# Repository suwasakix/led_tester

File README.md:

# LED Tester

LED テスター

&nbsp;

## 目次 - Contents

 - [このプリント基板について](#このプリント基板について---about-this-pcb)
 - [ガーバーデータのダウンロード](#ガーバーデータのダウンロード---download-gerber-data)
 - [回路図](#回路図---pcb-schematic)
 - [レイアウト](#レイアウト---pcb-layout)
 - [部品リスト](#部品リスト---parts-list)
 - [便利なアイテム](#便利なアイテム---useful-items)
 - [使用例](#使用例---example-of-use)
 - [開発環境](#開発環境---development-environment)
 - [ライセンスについて](#ライセンスについて---license)

&nbsp;

## このプリント基板について - About this PCB

このプリント基板は、LED のテスター回路を実装したものです。  

この基板はボリュームで電流値をコントロール可能な定電流回路を実装しており、電流に応じた LED の照度や順方向電圧の確認に使用することができます。  

念のために書いておくと、[OptoSupply の LED テスター][AK_101860_LED_TESTER] が秋月電子通商で売っています。どちらを選ぶかはお好みで。  

&nbsp;

【 測定用基板シリーズ 】  

- [定電流ダイオード/定電圧ダイオード/FET 簡易測定器](https://github.com/suwasakix/simple_crd_zd_fet_tester)  
- [トランジスタ hFE 簡易測定器](https://github.com/suwasakix/simple_hfe_tester)  
- [FET バイアス測定器](https://github.com/suwasakix/fet_bias_tester)  
- LED テスター  

&nbsp;

## ガーバーデータのダウンロード - Download gerber data

こちらのページから「led_tester-gerber.zip」のファイルをダウンロードしてください。  

&emsp; https://www.github.com/suwasakix/led_tester/releases

このプロジェクトは、各自がプリント基板のガーバーデータをダウンロードして PCB 基板メーカーに基板製造を発注することを前提にしています。個人で発注可能な PCB 基板メーカーは国内外問わずありますが、近年では 10cm 四方以下の基板サイズであれば海外メーカーで格安に製造委託することが可能になりました。発注例として、深圳の Seeed studio が提供する PCB 製造サービス「[Fusion PCB](https://www.fusionpcb.jp)」に基板製造を発注する方法を[こちらのページ](docs/ORDER_PCB.md)で紹介しておきます。  

&nbsp;

## 回路図 - PCB schematic

定電流回路はオペアンプを使用したオーソドックスな回路です。オペアンプには差動入力（＋端子と－端子）が同じ電圧となろうとする性質があるので、LED に電流が流ているとき VR1 の両端にかかる電圧と R1 の両端にかかる電圧はほぼ同じ値になります（R2 に電流はほとんど流れません）。VR1 を調整することによって LED に流れる電流をコントロールすることができるという仕組みです。  

Vcc (9V) を 12.4kΩ と 10kΩ で分圧したとき 10kΩ には約4V の電圧がかかることになるので、VR1 を調整することによって LED に流れる電流を最大 40mA 程度にまで変えることが可能です。ですが、最大電流が大きいと 1mA 単位の調整が難しくなるので、R4 を 18kΩ～22kΩ にして最大 20mA くらいにした方が使いやすいかもしれません。分圧比は各自の好みに応じて変更して頂いて問題ありませんが、最大電流は 50mA を超えないようにしてください。  

R1 は電流値を測定するための抵抗なので高精度品か、あるいは抵抗値を実測してなるべく 100Ω に近いものを使用してください。ワット数は 1/2W 以上のものを使用してください。  

R2 は他の作例を参考にして入れたものですが、おそらく 0Ω でも問題なく動作すると思います。  

VR1 には秋月電子通商で取り扱いのある基板取付用ボリューム RK09D117000B を採用しました。ボリュームの軸が長いので鋸などで軸を切って使用する場合には、必ず軸側を保持して切り落とすようにしてください。ボリューム本体側を保持して軸を切ろうとすると、ボリュームにストレスがかかって故障の原因になります。  

電源には 12V または 15V の AC アダプターを使用してください。DC ジャックは 外径 5.5mm / 内径 2.1mm センタープラスのものが適合します。 

&nbsp;

## レイアウト - PCB layout

* 基板サイズ : W 70mm × H 70mm

&nbsp;

## 部品リスト - Parts list

* 通販による部品販売では、10個単位などでまとめ売りされている場合がしばしばあります。注文の際にはご注意ください。
* ★ は省略可。
* ☆ は使用しなければ省略可。

|部品種別			|記号					|部品名															|値				|個数		|入手ルート																											|
|:----:				|:----:					|:----:															|:----:			|:----:		|:----:																												|
|抵抗				|R1						|金属皮膜抵抗 1/2W												|100Ω			|1			|[高精度 金属皮膜抵抗 1/2W100Ω ±0.1%][AK_108509_R100]																|
|					|R2, R3					|金属皮膜抵抗 1/4W												|10kΩ			|2			|[超小型 金属皮膜抵抗 1W10kΩ 1袋100本入][AK_108839_R10k]															|
|					|R4						|金属皮膜抵抗 1/4W												|2.2kΩ～2.4kΩ	|1			|[超小型 金属皮膜抵抗 1W2.2kΩ 1袋100本入][AK_108832_R2.2k]															|
|ボリューム			|VR1					|基板取付用ボリューム 10kΩBカーブ<br>RK09D117000B				|10kΩ			|1			|[基板取付用ボリューム 10kΩB][AK_114827_VR10kB_RK09D117000B]<br>[ボリューム用ツマミ][AK_C_CKNOB]					|
|コンデンサ			|C1						|電解コンデンサ<br>(直径 6.3mm,<br>リードピッチ 2.5mm)			|100μF			|1			|[100μF35V105℃ ルビコンZLH][AK_102724_C35v100u]																	|
|					|C2						|積層セラミックコンデンサ<br>(リードピッチ 2.54mm)				|0.33μF		|1			|[積層セラミックコンデンサー 0.33μF50V X7R 2.54mmピッチ][AK_115937_C50v0.33u]										|
|					|C3						|積層セラミックコンデンサ<br>(リードピッチ 2.54mm)				|0.1μF			|1			|[積層セラミックコンデンサー 0.1μF50V X7R 2.54mm][AK_113582_C50v0.1u]												|
|FET				|Q1						|BS170															|-				|1			|[Nch MOSFET BS170-D27Z][AK_130394_BS170]																			|
|IC					|U1						|２回路単電源オペアンプ<br>LM358/LM2904							|-				|1			|[2回路入汎用オペアンプ NJM2904D][AK_109216_NJM2904D]																|
|					|U2						|TO-220型 9V ３端子レギュレータ									|-				|1			|[三端子レギュレーター 9V1.5A NJM7809FA][AK_100162_NJM7809FA]														|
|スイッチ			|SW1 ★					|トグルスイッチ<br>(3P 1回路2接点 ON-ON)						|-				|1			|[2MS1-T1-B4-M2-Q-E][AK_102399_SW_2MS1-T1-B4-M2-Q-E]<br>[2MS1-T1-B4-VS2-Q-E-S][AK_100300_SW_2MS1-T1-B4-VS2-Q-E-S]	|
|チェック端子		|TP1 ～ TP5 ☆			|チェック端子													|-				|5			|[チェック端子][AK_C_CCHECKTER]																						|
|ソケット			|J1						|基板型DCジャック<br>(内径2.1mm, 外径5.5mm, 定格15V以上)		|-				|1			|[2DC0005D100 1パック4個入][AK_101604_2DC0005D100]																	|
|					|J2 ☆					|8ピン 板バネICソケット											|-				|1			|[2227-08-03 1パック10個入][AK_100017_2227-08-03]																	|
|基板スペーサー		|						|黄銅六角スペーサー<br>M3×10mm									|-				|4			|[FB3-10][AK_107313_FB3-10]																							|
|					|						|M3 ネジ								 						|-				|4			|(ホームセンター等で入手可能)																						|

[AK_108509_R100]:								https://akizukidenshi.com/catalog/g/g108509/
[AK_108832_R2.2k]:								https://akizukidenshi.com/catalog/g/g108832/
[AK_108839_R10k]:								https://akizukidenshi.com/catalog/g/g108839/
[AK_114827_VR10kB_RK09D117000B]:				https://akizukidenshi.com/catalog/g/g114827/
[DK_RK09D117000B]:								https://www.digikey.jp/ja/products/detail/alps-alpine/RK09D117000B/21721587
[AK_102724_C35v100u]:							https://akizukidenshi.com/catalog/g/g102724/
[AK_113582_C50v0.1u]:							https://akizukidenshi.com/catalog/g/g113582/
[AK_115937_C50v0.33u]:							https://akizukidenshi.com/catalog/g/g115937/
[AK_130394_BS170]:								https://akizukidenshi.com/catalog/g/g130394/
[AK_100162_NJM7809FA]:							https://akizukidenshi.com/catalog/g/g100162/
[AK_109216_NJM2904D]:							https://akizukidenshi.com/catalog/g/g109216/
[AK_102399_SW_2MS1-T1-B4-M2-Q-E]:				https://akizukidenshi.com/catalog/g/g102399/
[AK_100300_SW_2MS1-T1-B4-VS2-Q-E-S]:			https://akizukidenshi.com/catalog/g/g100300/
[AK_C_CKNOB]:									https://akizukidenshi.com/catalog/c/cknob/
[AK_C_CCHECKTER]:								https://akizukidenshi.com/catalog/c/ccheckter/
[AK_101604_2DC0005D100]:						https://akizukidenshi.com/catalog/g/g101604/
[AK_100017_2227-08-03]:							https://akizukidenshi.com/catalog/g/g100017/
[AK_107313_FB3-10]:								https://akizukidenshi.com/catalog/g/g107313/
[AK_116915_LED_OSO5PA5A33A-1MA]:				https://akizukidenshi.com/catalog/g/g116915/
[SG_EEHD-65V4_LED_L053PSRD]:					https://www.sengoku.co.jp/mod/sgk_cart/detail.php?code=EEHD-65V4
[SG_EEHD-53AM_LED_L053YD]:						https://www.sengoku.co.jp/mod/sgk_cart/detail.php?code=EEHD-53AM
[SG_EEHD-4FE4_LED_L053GD]:						https://www.sengoku.co.jp/mod/sgk_cart/detail.php?code=EEHD-4FE4
[AK_101860_LED_TESTER]:							https://akizukidenshi.com/catalog/g/g101860/

R1 は金属皮膜抵抗の高精度品を使用するか、あるいは誤差±1%の金属皮膜抵抗から選別したものを割り当てます。普及価格帯のデジタルマルチメーターの場合、抵抗値の確度（測定誤差）はおおよそ ±0.5% ～ ±1.0% といったところなので、高精度品を使用した方が外れは少ないことになります。ただし、高精度品を使用する場合でも部品の不良チェックのために抵抗値は実測しておくようにしてください。  

VR1 の RK09D117000B は秋月電子通商のほかに [DigiKey][DK_RK09D117000B] などでも取り扱いがあります。  

U1 のオペアンプは、基板に [ICソケット][AK_100017_2227-08-03] を取り付けてソケットにオペアンプを挿した方が融通が利きます。  

SW1 は電源スイッチですが、省略することもできます。省略する場合は JP1 のパターンをショートしてください。  

J2 は LED 用のソケットです。使わないソケットは省略することもできます。TP2 ～ TP3 から線出しして IC クリップで測定する LED を繋いでもよいです。  

&nbsp;

## 便利なアイテム - Useful items

|部品名																			|入手ルート																																				|
|:----:																			|:----:																																					|
|ACアダプター 12V<br>(DCプラグ内径2.1mm, 外径5.5mm,<br>センタープラス)			|[M120100-A010JP][AK_117429_ACDC12V_M120100-A010JP]<br>[AD-M120P100][AK_111994_ACDC12V_AD-M120P100]<br>[AD-K120P100][AK_106642_ACDC12V_AD-K120P100]		|
|ACアダプター 15V<br>(DCプラグ内径2.1mm, 外径5.5mm,<br>センタープラス)			|[ATS024T-W150U][AK_108404_ACDC15V_ATS024T-W150U]<br>[AD-B150P80][AK_111994_ACDC15V_AD-B150P80]															|
|テストリード<br>(バナナプラグ ⇔ ICクリップ)									|[TLA-106][AK_112359_TLA-106]																															|
|テストリード<br>(ICクリップ両端)												|[TLA-105][AK_112419_TLA-105]<br>[TLA-101][AK_111765_TLA-101]																							|

[AK_117429_ACDC12V_M120100-A010JP]:				https://akizukidenshi.com/catalog/g/g117429/
[AK_111994_ACDC12V_AD-M120P100]:				https://akizukidenshi.com/catalog/g/g111994/
[AK_106642_ACDC12V_AD-K120P100]:				https://akizukidenshi.com/catalog/g/g106642/
[AK_108404_ACDC15V_ATS024T-W150U]:				https://akizukidenshi.com/catalog/g/g108404/
[AK_111994_ACDC15V_AD-B150P80]:					https://akizukidenshi.com/catalog/g/g111999/
[AK_112359_TLA-106]:							https://akizukidenshi.com/catalog/g/g112359/
[AK_112419_TLA-105]:							https://akizukidenshi.com/catalog/g/g112419/
[AK_111765_TLA-101]:							https://akizukidenshi.com/catalog/g/g111765/

## 使用例 - Example of use

写真は [OptoSupply OSO5PA5A33A-1MA][AK_116915_LED_OSO5PA5A33A-1MA] を測定した例で、1mA 流したときの順方向電圧は 1.86V です。  

何種類かの LED を２個ずつ実測した結果を下表に示します。LED の順方向電圧は型番によって違いがありますが、電流が少ない範囲内では個体差はほぼないといえそうです。  

|型番																|1.0mA		|2.0mA		|5.0mA		|10mA		|20mA		|
|:----:																|:----:		|:----:		|:----:		|:----:		|:----:		|
|[OptoSupply OSO5PA5A33A-1MA][AK_116915_LED_OSO5PA5A33A-1MA]		|1.85V		|1.89V		|1.98V		|2.08V		|2.24V		|
|〃																	|1.85V		|1.90V		|1.99V		|2.11V		|2.29V		|
|[LENOO L053PSRD][SG_EEHD-65V4_LED_L053PSRD]						|1.70V		|1.73V		|1.77V		|1.81V		|1.84V		|
|〃																	|1.70V		|1.73V		|1.77V		|1.81V		|1.85V		|
|[LENOO L053YD][SG_EEHD-53AM_LED_L053YD]							|1.79V		|1.83V		|1.91V		|2.00V		|2.14V		|
|〃																	|1.79V		|1.83V		|1.91V		|2.00V		|2.15V		|
|[LENOO L053GD][SG_EEHD-4FE4_LED_L053GD]							|1.87V		|1.92V		|1.99V		|2.09V		|2.24V		|
|〃																	|1.88V		|1.92V		|1.99V		|2.08V		|2.24V		|

&nbsp;

## 開発環境 - Development environment

このプリント基板の設計データは、[KiCad](https://www.kicad.org) 9.0 で作成しています。基板のデータは KiCad 9.0 以降で編集することができます。  

なお、この基板のデータを改変するには KiCad ライブラリ [Victwale](https://github.com/suwasakix/Victwale) を必要とします。  

&nbsp;

## ライセンスについて - License

このプリント基板の設計データのライセンスは [Creative Commons CC-BY 4.0 License](https://creativecommons.org/licenses/by/4.0/legalcode) です。

- 上記設計データの著作権は作者 (suwasakix) が保持します。ただし、著作権が生じるのは設計データのレイアウトのみであり、回路図に著作権は生じません。

- 上記設計データは、何の制限もなく私的に利用することができます。データを自由に改変して私的に利用することもできます。

- 上記設計データに変更を加えることなく製造したプリント基板は、商用・非商用を問わず何の制限もなく第三者に頒布することができます。

- 上記設計データの改変物、または改変物をもとに製造したプリント基板（二次創作物）を第三者に頒布するには、原作品が著作権者 (suwasakix) のものであること、および当該作品が二次創作物であることを明示する必要があります。一例としては、原作品の著作権者、および二次創作物の著作権者を当該作品に明示すれば問題ありません。

  - なお、それらを明示する手段は当該作品の実物以外に、当該作品の設計データの一時配布元でもよいものとします（当該作品に著作権者の情報を記載する物理的なスペースがない場合には、一時配布元に著作権者の情報を記載することで代えることが可能です）。その場合、当該作品の実物にデータの一時配布元が記載されていなければなりません。

- 上記設計データの二次創作物には、原作品とは異なるライセンスを適用することができます。

- 上記ライセンスは著作権者からの一方的な利用許諾条件です。利用するにあたり著作権者への連絡は一切不要です。

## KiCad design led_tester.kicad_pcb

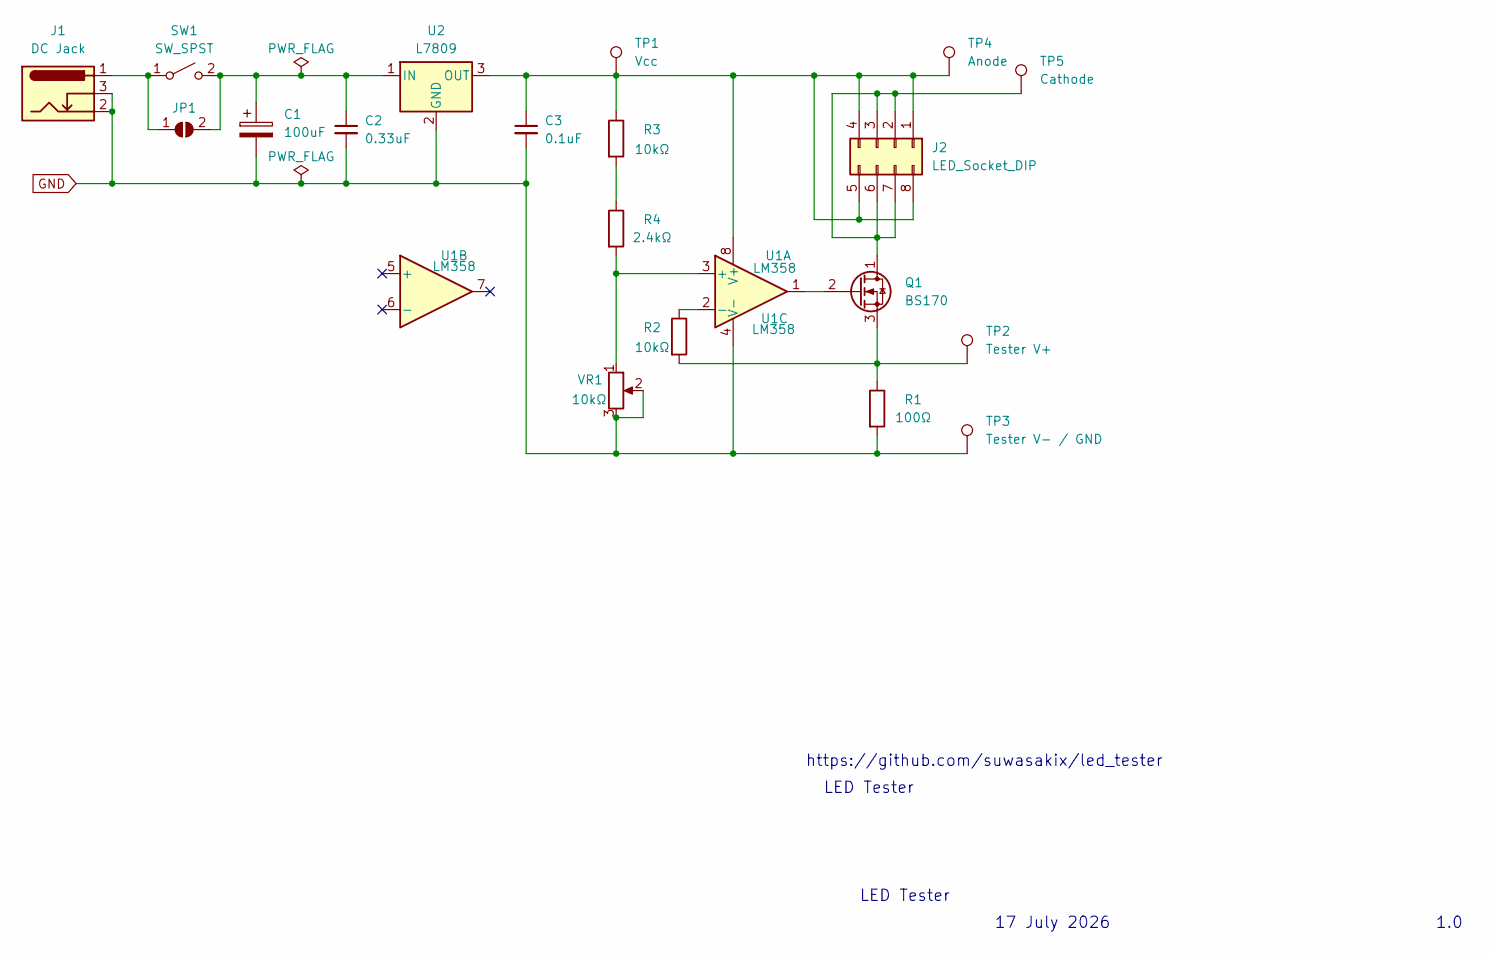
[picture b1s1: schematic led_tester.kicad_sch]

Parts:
C1: 100uF; CP_Radial_D6.3mm_P2.50mm
C2: 0.33uF; C_Disc_D5.0mm_W2.5mm_P2.50mm
C3: 0.1uF; C_Disc_D5.0mm_W2.5mm_P2.50mm
J1: DC Jack; BarrelJack_Horizontal
J2: LED_Socket_DIP; DIP-8_W7.62mm_Socket
JP1: SolderJumper-2_P1.3mm_Open_TrianglePad1.0x1.5mm
Q1: BS170; TO-92_Inline_Wide
R1: 100Ω; R_Axial_DIN0411_L9.9mm_D3.6mm_P12.70mm_Horizontal
R2, R3: 10kΩ; R_Axial_DIN0207_L6.3mm_D2.5mm_P7.62mm_Horizontal
R4: 2.4kΩ; R_Axial_DIN0207_L6.3mm_D2.5mm_P7.62mm_Horizontal
SW1: SW_SPST; SW_DPDT_2MS1-T1-B4-VS2-Q-E
TP1: Vcc; Pin_D1.0mm_L10.0mm
TP2: Tester V+; Pin_D1.0mm_L10.0mm
TP3: Tester V- / GND; Pin_D1.0mm_L10.0mm
TP4: Anode; Pin_D1.0mm_L10.0mm
TP5: Cathode; Pin_D1.0mm_L10.0mm
U1: LM358; DIP-8_W7.62mm_Socket
U2: L7809; TO-220F-3_Horizontal_TabDown
VR1: 10kΩ; Potentiometer_Alps_RK09K_Single_Vertical

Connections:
GND: C1.2, C2.2, C3.2, J1.2, J1.3, R1.2, TP3.1, U1.4 (V-), U2.2 (GND), VR1.2, VR1.3
unnamed: C3.1, J2.1, J2.4, J2.5, J2.8, R3.1, TP1.1, TP4.1, U1.8 (V+), U2.3 (OUT)
unnamed: J2.2, J2.3, J2.6, J2.7, Q1.1 (D), TP5.1
unnamed: J1.1, JP1.1 (A), SW1.1 (A)
unnamed: C1.1, C2.1, JP1.2 (B), SW1.2 (B), U2.1 (IN)
unnamed: Q1.2 (G), U1.1
unnamed: Q1.3 (S), R1.1, R2.2, TP2.1
unnamed: R3.2, R4.1
unnamed: R4.2, U1.3 (+), VR1.1
unnamed: R2.1, U1.2 (-)

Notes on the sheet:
LED Tester
1.0
17 July 2026
https://github.com/suwasakix/led_tester

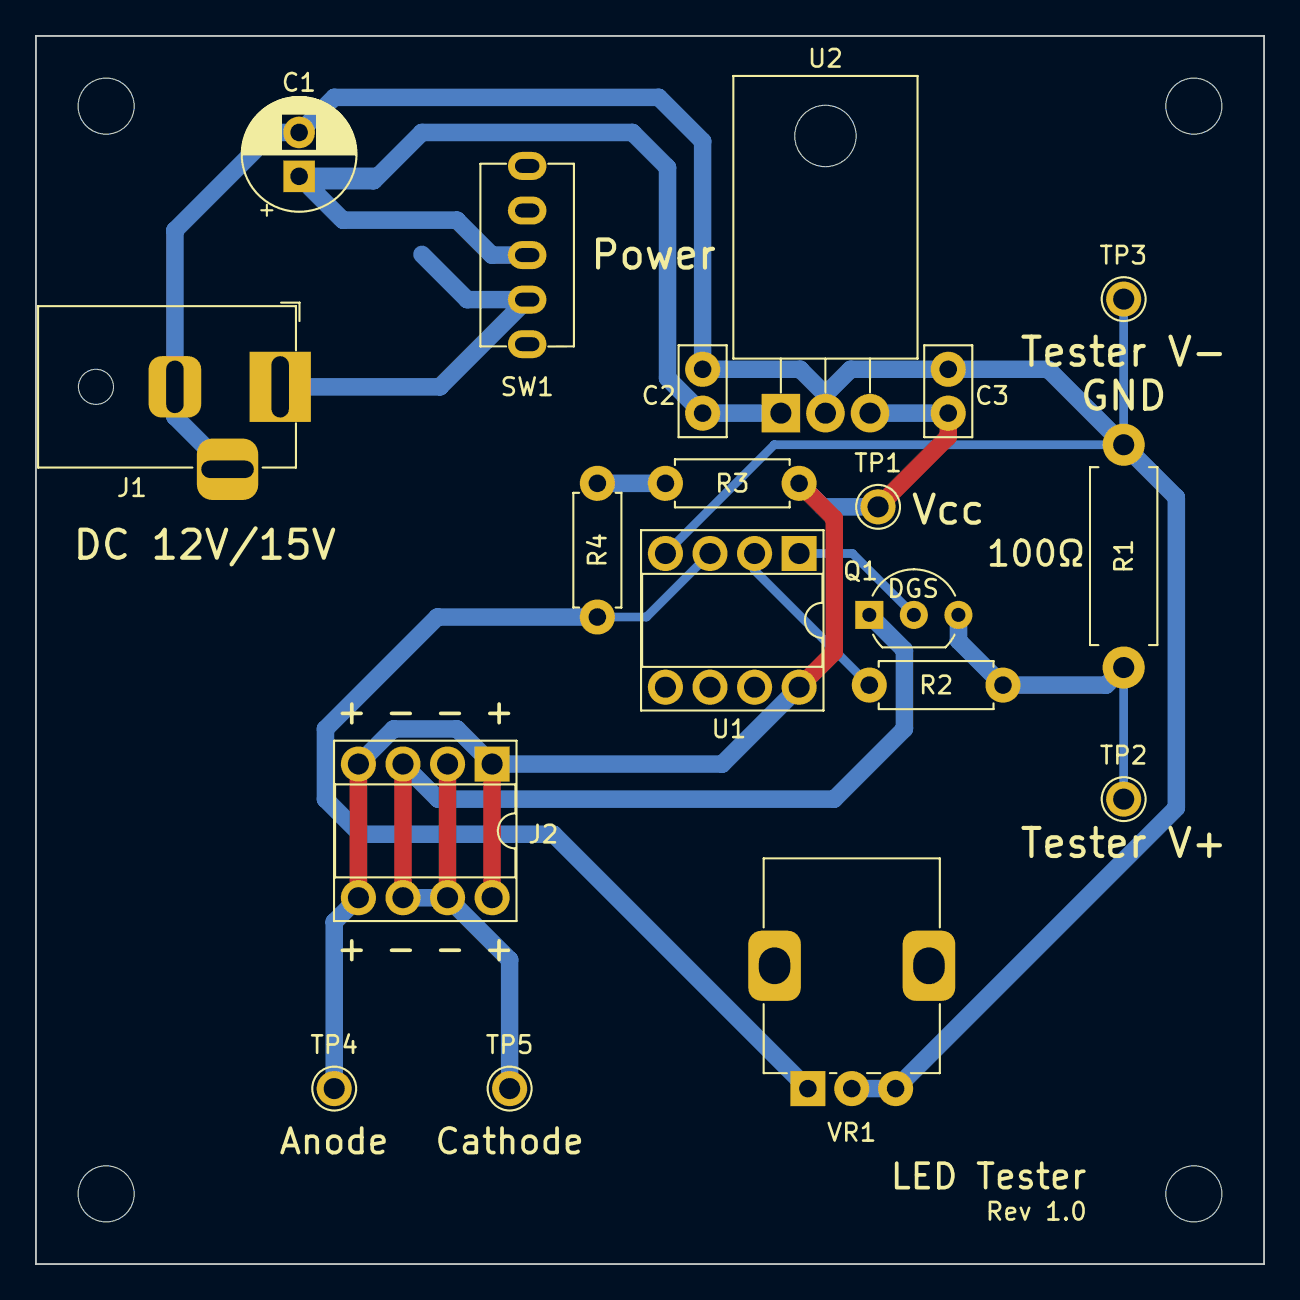
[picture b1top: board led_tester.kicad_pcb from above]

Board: 2 copper layers, 70.0 x 70.0 mm, 20 parts (1 on the bottom side), 10 nets.

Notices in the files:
led_tester.kicad_pcb:
© suwasakix 2026, licensed under CC-BY-4.0
